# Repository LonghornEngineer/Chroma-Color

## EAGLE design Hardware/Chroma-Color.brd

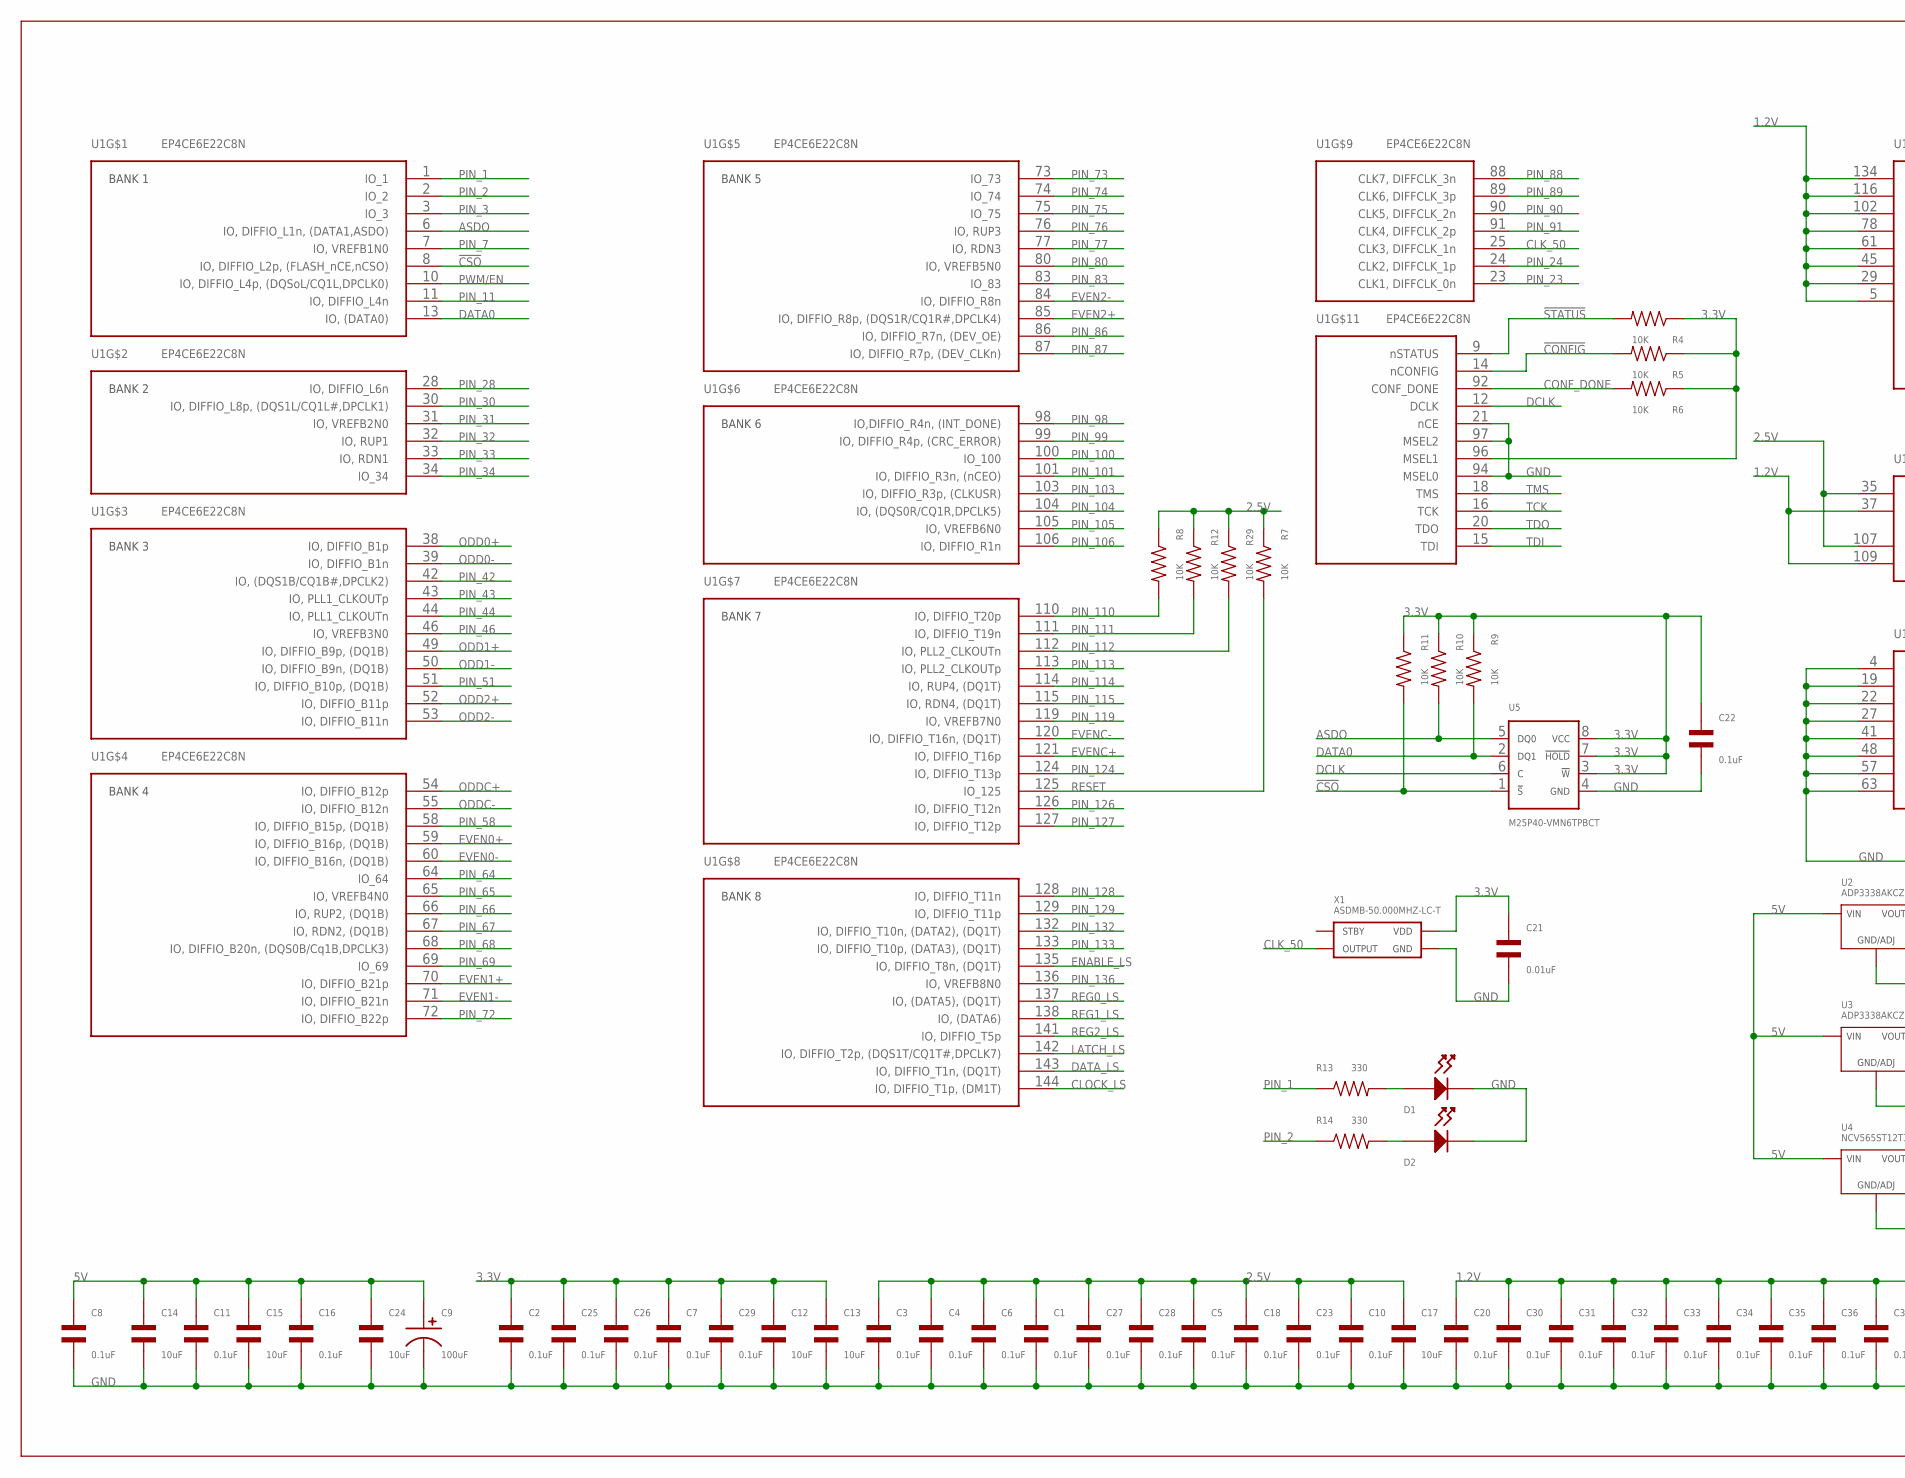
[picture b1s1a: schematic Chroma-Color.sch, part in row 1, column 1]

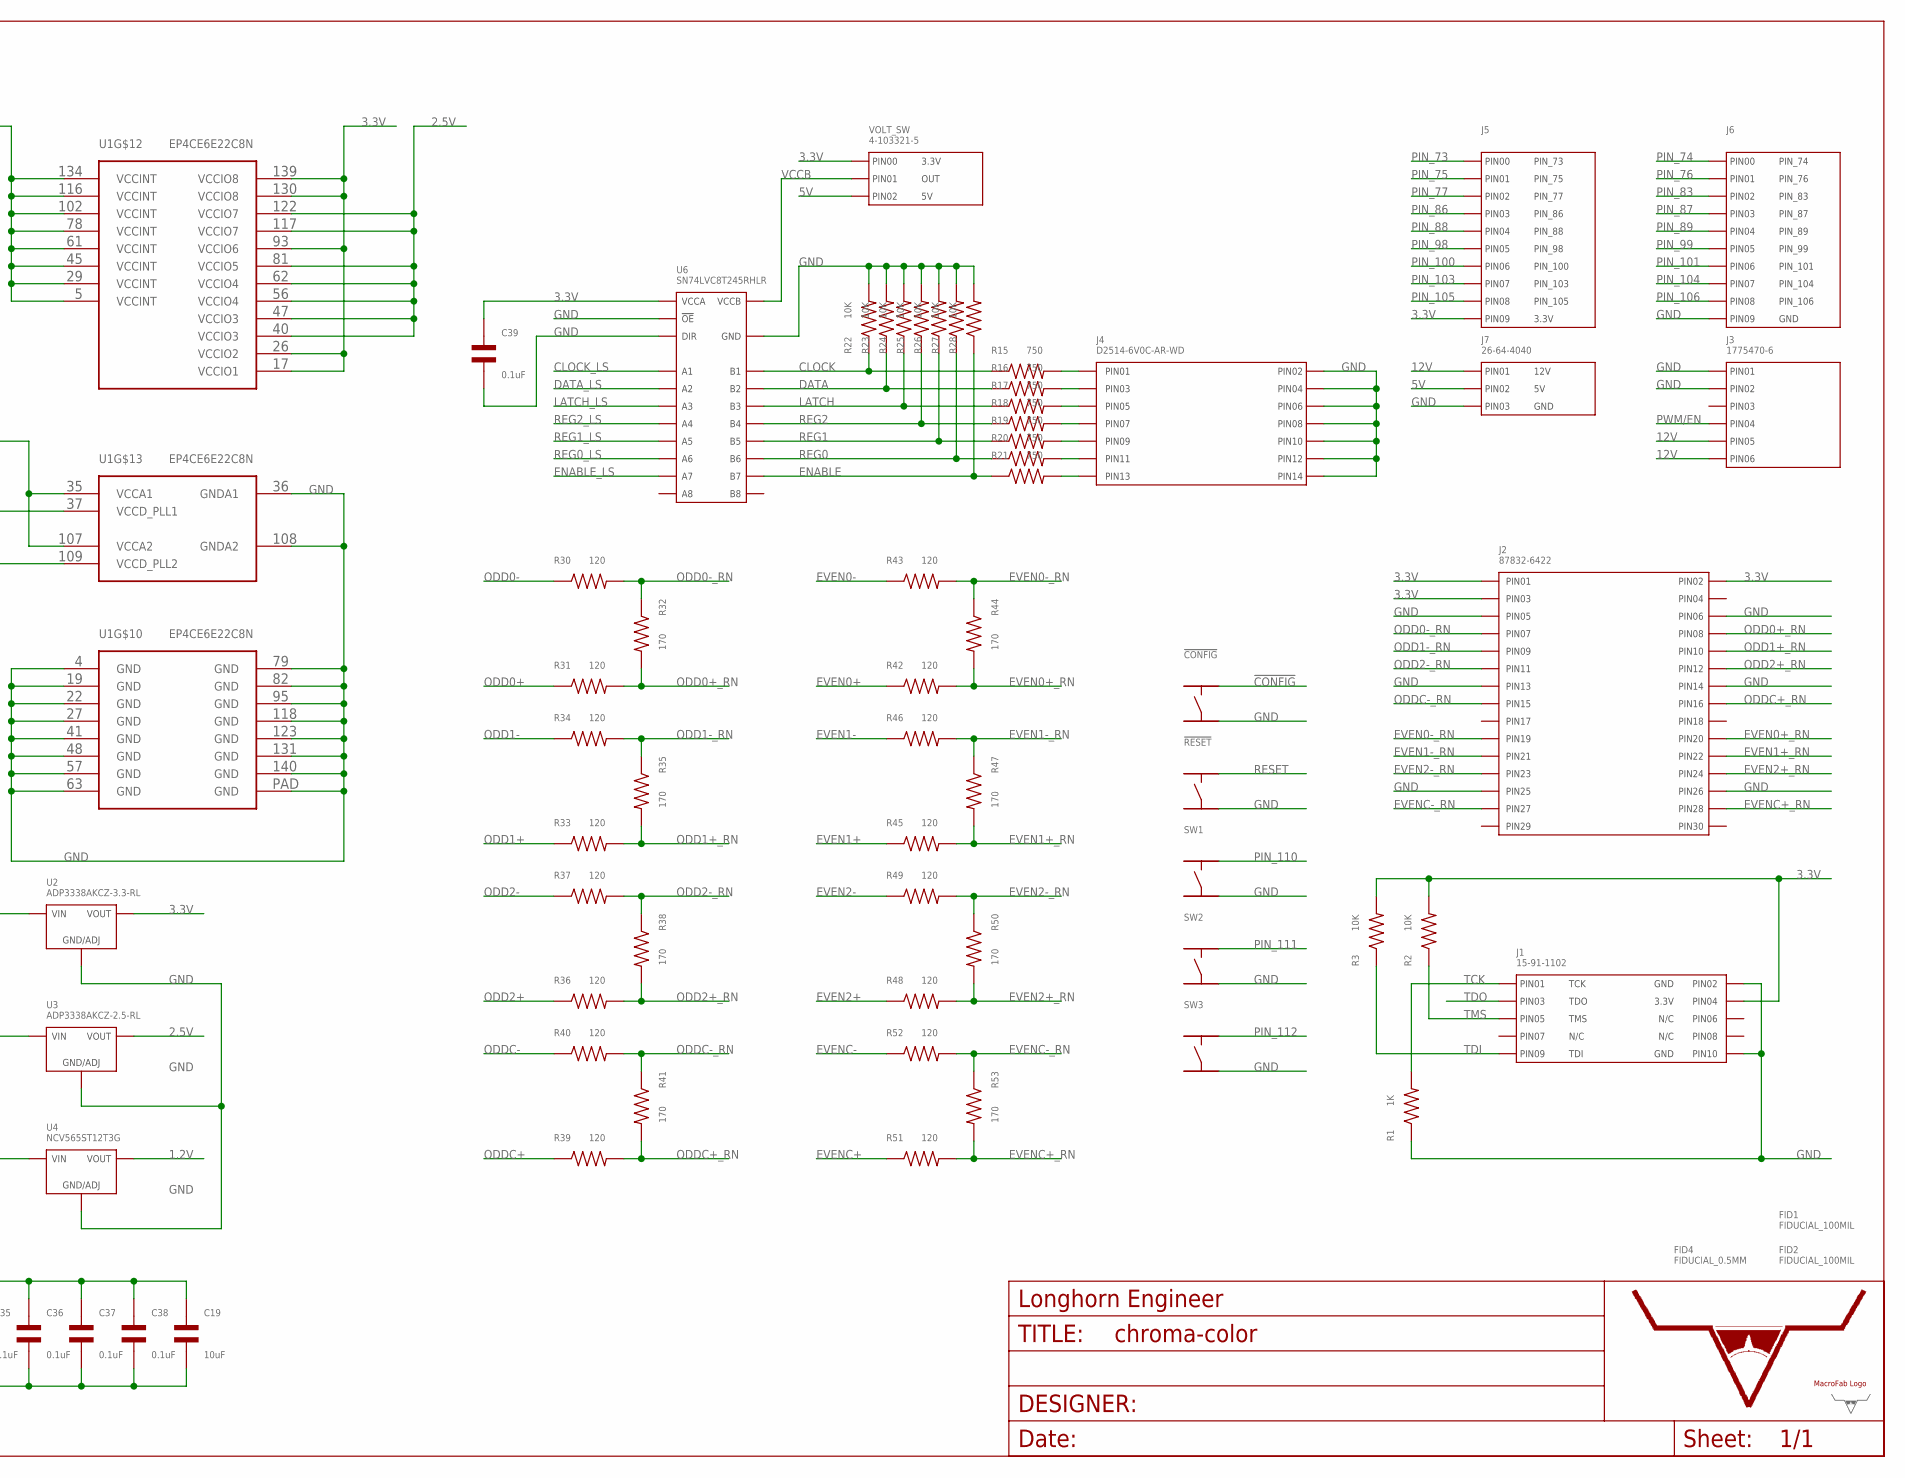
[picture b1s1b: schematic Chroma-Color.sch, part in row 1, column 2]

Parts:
!CONFIG: TACT_4.2MM; TACT4.2MM
!RESET: TACT_4.2MM; TACT4.2MM
C1, C2, C3, C4, C5, C6, C7, C8, C10, C11, C16, C18, C20, C22, C23, C25, C26, C27, C28, C29, C30, C31, C32, C33, C34, C35, C36, C37, C38, C39: 0.1uF; C0603
C9: 100uF; CP6.3MM
C12, C13, C14, C15, C17, C19, C24: 10uF; C0603
C21: 0.01uF; C0603
D1, D2: LED_SINGLE_0805; LED0805
FID1, FID2: FIDUCIAL_100MIL
FID4: FIDUCIAL_0.5MM
J1: 15-91-1102
J2: 87832-6422
J3: 1775470-6
J4: D2514-6V0C-AR-WD
J5, J6: HEADER_01X10_PTH_2.54MM; PTH_2.54MM_01X10
J7: 26-64-4040; 26-64-4040(KEYPIN1)
R1: 1K; R0603
R2, R3, R4, R5, R6, R7, R8, R9, R10, R11, R12, R22, R23, R24, R25, R26, R27, R28, R29: 10K; R0603
R13, R14: 330; R0603
R15, R16, R17, R18, R19, R20, R21: 750; R0603
R30, R31, R33, R34, R36, R37, R39, R40, R42, R43, R45, R46, R48, R49, R51, R52: 120; R0402
R32, R35, R38, R41, R44, R47, R50, R53: 170; R0402
SW1, SW2, SW3: TACT_4.2MM; TACT4.2MM
U1: EP4CE6E22C8N; EQFP-144
U2: ADP3338AKCZ-3.3-RL; ADP3338_SOT-223-3
U3: ADP3338AKCZ-2.5-RL; ADP3338_SOT-223-3
U4: NCV565ST12T3G; NCV565_SOT-223-3
U5: M25P40-VMN6TPBCT; M25P40_SOIC-8
U6: SN74LVC8T245RHLR; SN74LVC8T245_VQFN-24
U$1: LHE_FRAME
U$2: MF_LOGOLOGO_MEDIUM; MF_LOGO_MEDIUM
U$3: LHE_LOGOLHE_LOGO; LHE_LOGO
VOLT_SW: 4-103321-5; PTH_2.54MM_01X03
X1: ASDMB-50.000MHZ-LC-T; ASDMB

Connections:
1.2V: C19.P$1, C20.P$1, C30.P$1, C31.P$1, C32.P$1, C33.P$1, C34.P$1, C35.P$1, C36.P$1, C37.P$1, C38.P$1, U1.5, U1.29, U1.37, U1.45, U1.61, U1.78, U1.102, U1.109, U1.116, U1.134, U4.2 (OUT), U4.PAD (OUT)
2.5V: C1.P$1, C3.P$1, C4.P$1, C5.P$1, C6.P$1, C10.P$1, C17.P$1, C18.P$1, C23.P$1, C27.P$1, C28.P$1, R7.P$1, R8.P$1, R12.P$1, R29.P$1, U1.35, U1.40, U1.47, U1.56, U1.62, U1.81, U1.107, U1.117, U1.122, U3.2 (OUT), U3.PAD (OUT)
3.3V: C2.P$1, C7.P$1, C12.P$1, C13.P$1, C21.P$1, C22.P$1, C25.P$1, C26.P$1, C29.P$1, C39.P$1, J1.4 (PIN4), J2.P$1 (PIN0), J2.P$2 (PIN1), J2.P$3 (PIN2), J5.P$10 (PIN9), R2.P$2, R3.P$2, R4.P$1, R5.P$1, R6.P$1, R9.P$1, R10.P$1, R11.P$1, U1.17, U1.26, U1.93, U1.96, U1.130, U1.139, U2.2 (OUT), U2.PAD (OUT), U5.3 (!W), U5.7 (!HOLD), U5.8 (VCC), U6.1 (VCCA), VOLT_SW.P$1 (PIN0), X1.P$4 (VDD)
5V: C8.P$1, C9.P$1, C11.P$1, C14.P$1, C15.P$1, C16.P$1, C24.P$1, J7.3 (PIN2), U2.3 (IN), U3.3 (IN), U4.3 (IN), VOLT_SW.P$3 (PIN2)
12V: J3.P$5 (5), J3.P$6 (6), J7.2 (PIN1)
!CONFIG: !CONFIG.P$2, R5.P$2, U1.14
!CSO: R11.P$2, U1.8, U5.1 (!S)
!STATUS: R4.P$2, U1.9
ASDO: R10.P$2, U1.6, U5.5 (DQ0)
CLK_50: U1.25, X1.P$3 (OUTPUT)
CLOCK: R15.P$1, R22.P$1, U6.21 (B1)
CLOCK_LS: U1.144, U6.3 (A1)
CONF_DONE: R6.P$2, U1.92
DATA: R16.P$1, R23.P$1, U6.20 (B2)
DATA0: R9.P$2, U1.13, U5.2 (DQ1)
DATA_LS: U1.143, U6.4 (A2)
DCLK: U1.12, U5.6 (C)
ENABLE: R21.P$1, R28.P$1, U6.15 (B7)
ENABLE_LS: U1.135, U6.9 (A7)
EVEN0+: R42.P$1, U1.59
EVEN0+_RN: J2.P$20 (PIN19), R42.P$2, R44.P$2
EVEN0-: R43.P$1, U1.60
EVEN0-_RN: J2.P$19 (PIN18), R43.P$2, R44.P$1
EVEN1+: R45.P$1, U1.70
EVEN1+_RN: J2.P$22 (PIN21), R45.P$2, R47.P$2
EVEN1-: R46.P$1, U1.71
EVEN1-_RN: J2.P$21 (PIN20), R46.P$2, R47.P$1
EVEN2+: R48.P$1, U1.85
EVEN2+_RN: J2.P$24 (PIN23), R48.P$2, R50.P$2
EVEN2-: R49.P$1, U1.84
EVEN2-_RN: J2.P$23 (PIN22), R49.P$2, R50.P$1
EVENC+: R51.P$1, U1.121
EVENC+_RN: J2.P$28 (PIN27), R51.P$2, R53.P$2
EVENC-: R52.P$1, U1.120
EVENC-_RN: J2.P$27 (PIN26), R52.P$2, R53.P$1
GND: !CONFIG.P$4, !RESET.P$4, C1.P$2, C2.P$2, C3.P$2, C4.P$2, C5.P$2, C6.P$2, C7.P$2, C8.P$2, C9.P$2, C10.P$2, C11.P$2, C12.P$2, C13.P$2, C14.P$2, C15.P$2, C16.P$2, C17.P$2, C18.P$2, C19.P$2, C20.P$2, C21.P$2, C22.P$2, C23.P$2, C24.P$2, C25.P$2, C26.P$2, C27.P$2, C28.P$2, C29.P$2, C30.P$2, C31.P$2, C32.P$2, C33.P$2, C34.P$2, C35.P$2, C36.P$2, C37.P$2, C38.P$2, C39.P$2, D1.CATHODE, D2.CATHODE, J1.2 (PIN2), J1.10 (PIN10), J2.P$5 (PIN4), J2.P$6 (PIN5), J2.P$13 (PIN12), J2.P$14 (PIN13), J2.P$25 (PIN24), J2.P$26 (PIN25), J3.P$1 (1), J3.P$2 (2), J4.2 (PIN2), J4.4 (PIN4), J4.6 (PIN6), J4.8 (PIN8), J4.10 (PIN10), J4.12 (PIN12), J4.14 (PIN14), J6.P$10 (PIN9), J7.4 (PIN3), R1.P$1, R22.P$2, R23.P$2, R24.P$2, R25.P$2, R26.P$2, R27.P$2, R28.P$2, SW1.P$4, SW2.P$4, SW3.P$4, U1.4, U1.19, U1.21, U1.22, U1.27, U1.36, U1.41, U1.48, U1.57, U1.63, U1.79, U1.82, U1.94, U1.95, U1.97, U1.108, U1.118, U1.123, U1.131, U1.140, U1.PAD (145), U2.1 (GND), U3.1 (GND), U4.1 (GND), U5.4 (GND), U6.2 (DIR), U6.11 (GND), U6.12 (GND), U6.13 (GND), U6.22 (!OE), X1.P$2 (GND)
LATCH: R17.P$1, R24.P$1, U6.19 (B3)
LATCH_LS: U1.142, U6.5 (A3)
unnamed: D1.ANODE, R13.P$2
unnamed: D2.ANODE, R14.P$2
unnamed: J4.1 (PIN1), R15.P$2
unnamed: J4.3 (PIN3), R16.P$2
unnamed: J4.5 (PIN5), R17.P$2
unnamed: J4.7 (PIN7), R18.P$2
unnamed: J4.9 (PIN9), R19.P$2
unnamed: J4.11 (PIN11), R20.P$2
unnamed: J4.13 (PIN13), R21.P$2
ODD0+: R31.P$1, U1.38
ODD0+_RN: J2.P$8 (PIN7), R31.P$2, R32.P$2
ODD0-: R30.P$1, U1.39
ODD0-_RN: J2.P$7 (PIN6), R30.P$2, R32.P$1
ODD1+: R33.P$1, U1.49
ODD1+_RN: J2.P$10 (PIN9), R33.P$2, R35.P$2
ODD1-: R34.P$1, U1.50
ODD1-_RN: J2.P$9 (PIN8), R34.P$2, R35.P$1
ODD2+: R36.P$1, U1.52
ODD2+_RN: J2.P$12 (PIN11), R36.P$2, R38.P$2
ODD2-: R37.P$1, U1.53
ODD2-_RN: J2.P$11 (PIN10), R37.P$2, R38.P$1
ODDC+: R39.P$1, U1.54
ODDC+_RN: J2.P$16 (PIN15), R39.P$2, R41.P$2
ODDC-: R40.P$1, U1.55
ODDC-_RN: J2.P$15 (PIN14), R40.P$2, R41.P$1
PIN_1: R13.P$1, U1.1
PIN_2: R14.P$1, U1.2
PIN_3: U1.3
PIN_7: U1.7
PIN_11: U1.11
PIN_23: U1.23
PIN_24: U1.24
PIN_28: U1.28
PIN_30: U1.30
PIN_31: U1.31
PIN_32: U1.32
PIN_33: U1.33
PIN_34: U1.34
PIN_42: U1.42
PIN_43: U1.43
PIN_44: U1.44
PIN_46: U1.46
PIN_51: U1.51
PIN_58: U1.58
PIN_64: U1.64
PIN_65: U1.65
PIN_66: U1.66
PIN_67: U1.67
PIN_68: U1.68
PIN_69: U1.69
PIN_72: U1.72
PIN_73: J5.P$1 (PIN0), U1.73
PIN_74: J6.P$1 (PIN0), U1.74
PIN_75: J5.P$2 (PIN1), U1.75
PIN_76: J6.P$2 (PIN1), U1.76
PIN_77: J5.P$3 (PIN2), U1.77
PIN_80: U1.80
PIN_83: J6.P$3 (PIN2), U1.83
PIN_86: J5.P$4 (PIN3), U1.86
PIN_87: J6.P$4 (PIN3), U1.87
PIN_88: J5.P$5 (PIN4), U1.88
PIN_89: J6.P$5 (PIN4), U1.89
PIN_90: U1.90
PIN_91: U1.91
PIN_98: J5.P$6 (PIN5), U1.98
PIN_99: J6.P$6 (PIN5), U1.99
PIN_100: J5.P$7 (PIN6), U1.100
PIN_101: J6.P$7 (PIN6), U1.101
PIN_103: J5.P$8 (PIN7), U1.103
PIN_104: J6.P$8 (PIN7), U1.104
PIN_105: J5.P$9 (PIN8), U1.105
PIN_106: J6.P$9 (PIN8), U1.106
PIN_110: R8.P$2, SW1.P$2, U1.110
PIN_111: R12.P$2, SW2.P$2, U1.111
PIN_112: R29.P$2, SW3.P$2, U1.112
PIN_113: U1.113
PIN_114: U1.114
PIN_115: U1.115
PIN_119: U1.119
PIN_124: U1.124
PIN_126: U1.126
PIN_127: U1.127
PIN_128: U1.128
PIN_129: U1.129
PIN_132: U1.132
PIN_133: U1.133
PIN_136: U1.136
PWM/EN: J3.P$4 (4), U1.10
REG0: R20.P$1, R27.P$1, U6.16 (B6)
REG0_LS: U1.137, U6.8 (A6)
REG1: R19.P$1, R26.P$1, U6.17 (B5)
REG1_LS: U1.138, U6.7 (A5)
REG2: R18.P$1, R25.P$1, U6.18 (B4)
REG2_LS: U1.141, U6.6 (A4)
RESET: !RESET.P$2, R7.P$2, U1.125
TCK: J1.1 (PIN1), R1.P$2, U1.16
TDI: J1.9 (PIN9), R3.P$1, U1.15
TDO: J1.3 (PIN3), U1.20
TMS: J1.5 (PIN5), R2.P$1, U1.18
VCCB: U6.23 (VCCB), U6.24 (VCCB), VOLT_SW.P$2 (PIN1)

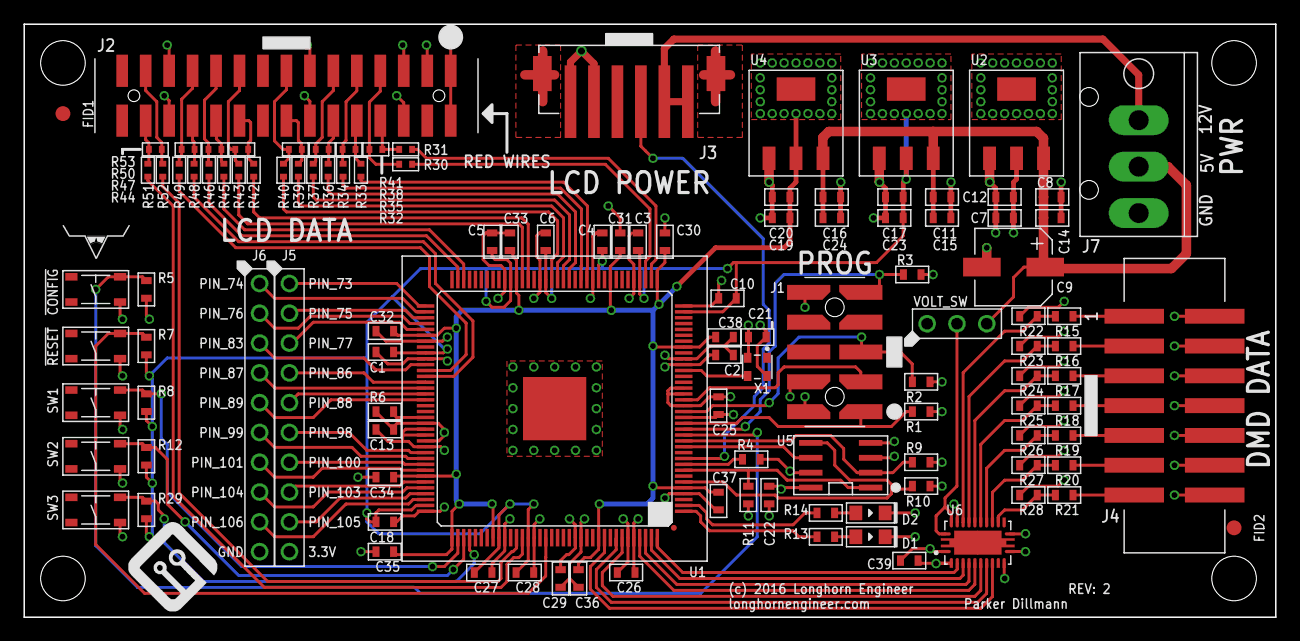
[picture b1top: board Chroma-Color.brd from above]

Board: 4 copper layers, 106.7 x 50.5 mm, 120 parts (0 on the bottom side), 99 nets.

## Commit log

2015-11-01 First push of stuff. FPGA almost done schematic.
2015-11-02 Added connectors and crystal
2015-11-02 Changed 4.7K to 10K resistors.
2015-11-03 Schematic done. Need new 2x7 con and start layout.
2015-11-04 Schematic done, Updated software with latest
    Connectors need physical testing before layout happens. DMD connector
    needs to be switched to SMT part
    D2514-6V0C-AR-WD.
2015-11-04 Added last 2x7 SMT connector
2015-11-05 Started Routing.
2015-11-06 Layout complete. Silkscreen next.
2015-11-06 Silkscreen done. Added 2SW and 2LED.
2015-11-06 Updated schematic picture.
2015-11-10 Added 750ohm and 10K pulldowns on DMD con.
2015-11-10 Increased board area to add material around mount holes.
2015-11-10 Added Fids. Working on Rail version.
2015-12-07 Rev2 start. Fixed JTAG programming cable.
2015-12-09 Fixed 3 PIN Power Connector.
2015-12-10 Updated connectors to latest library
2015-12-11 Fixed voltage regulators to use newer library
2015-12-11 changed 25MHz to 50Mhz
2015-12-14 Updated to latest library style.
2016-01-18 Added mark on LCD DATA cable for red wires.
2016-01-18 Updated Firmware.
2016-01-30 Added SW3. Need to add a buffer/level shifter.
2016-02-01 Working on adding level shifter and LVDS 3 R
2016-02-01 REV 2 done.
2016-02-01 Added manufacturing gerbers.
2016-02-16 updating license.
2016-09-03 updating code base.
2016-09-07 old screen datasheet.

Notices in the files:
parts and their libraries:
PP_Aesthetics: (c) 2016 Longhorn Engineer
